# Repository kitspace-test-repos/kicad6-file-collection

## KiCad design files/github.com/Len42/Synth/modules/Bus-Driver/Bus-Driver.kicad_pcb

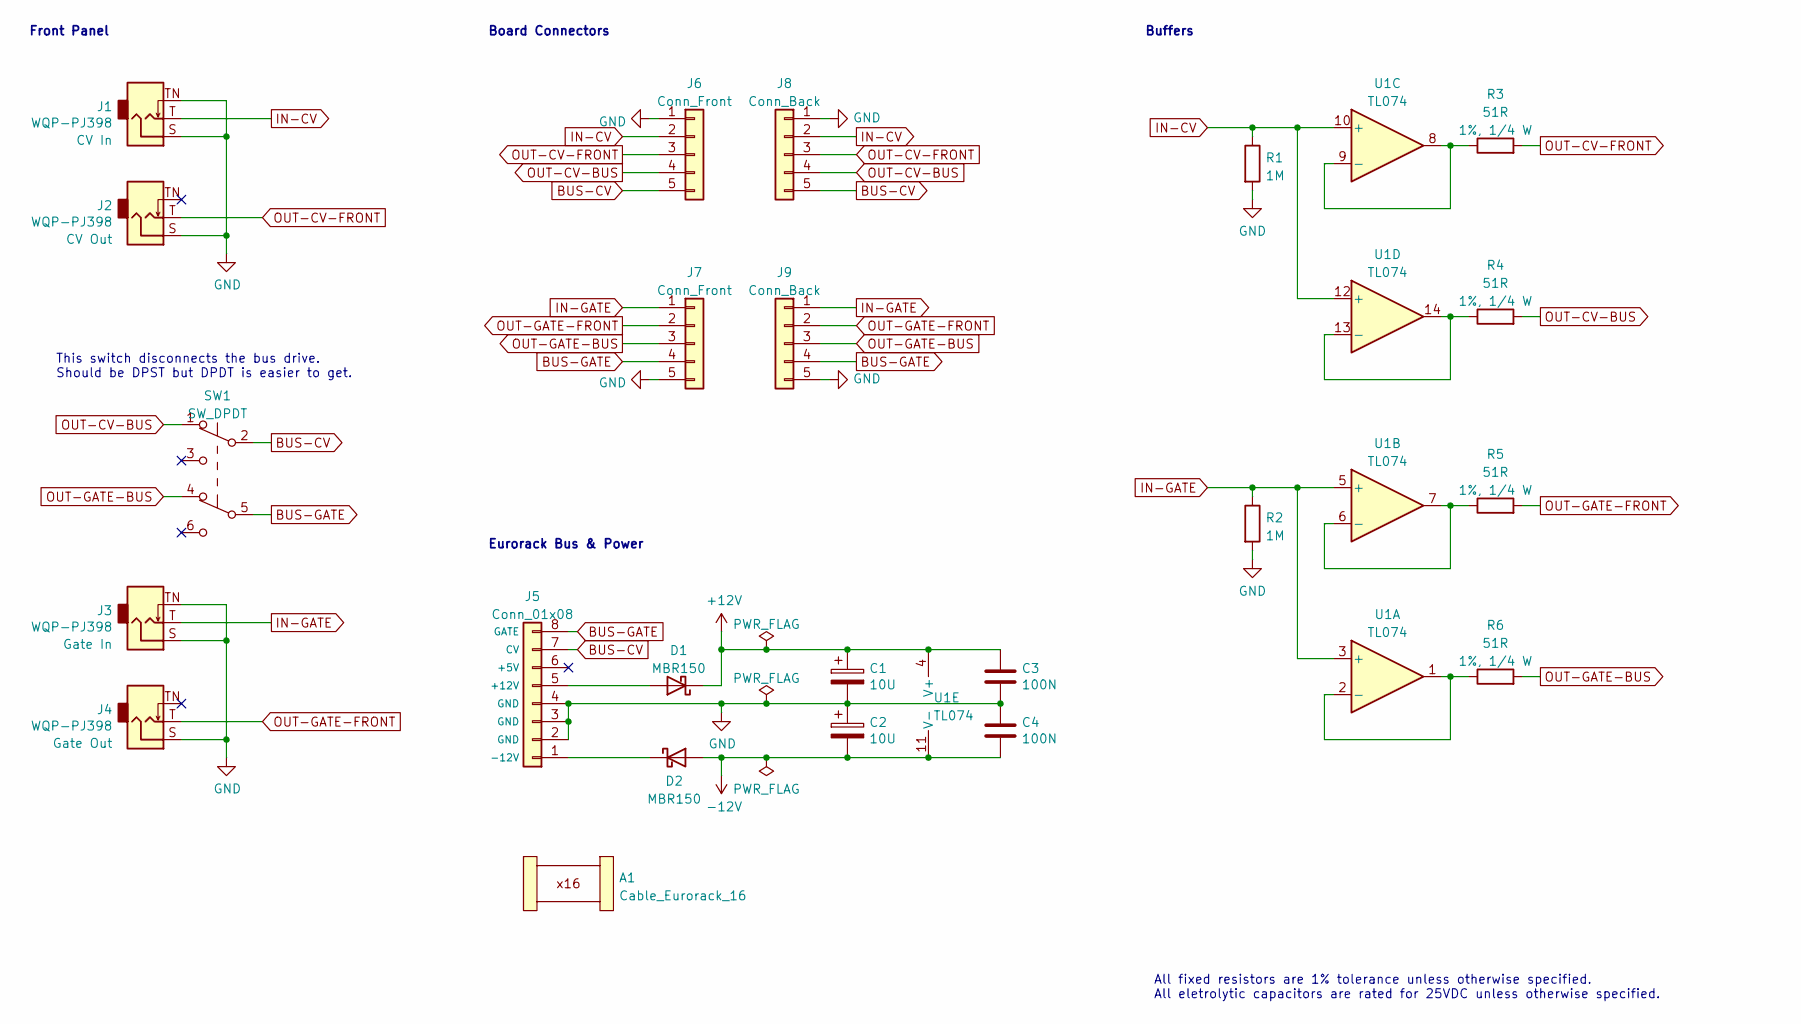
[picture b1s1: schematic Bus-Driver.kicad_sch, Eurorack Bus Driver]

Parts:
A1: Cable_Eurorack_16; NoFootprint
C1, C2: 10U; CP_Radial_D5.0mm_P2.50mm; ManufacturerPartNum ECE-A1VKS100I
C3, C4: 100N; C_Disc_D5.0mm_W2.5mm_P2.50mm; ManufacturerPartNum FG18X7R1H104KNT06
D1, D2: MBR150; D_DO-41_SOD81_P7.62mm_Horizontal; ManufacturerPartNum MBR150RLG
J1, J2, J3, J4: WQP-PJ398; Jack_3.5mm_QingPu_WQP-PJ398SM_Vertical; ManufacturerPartNum PJ398SM / WQP518MA
J5: Conn_01x08; PinHeader-Eurorack-8-TH-RA
J6, J7: Conn_Front; PinSocket_1x05_P2.54mm_Vertical
J8, J9: Conn_Back; PinHeader_1x05_P2.54mm_Horizontal
R1, R2: 1M; R_Axial_DIN0207_L6.3mm_D2.5mm_P7.62mm_Horizontal; ManufacturerPartNum MFR-12*
R3, R4, R5, R6: 51R; R_Axial_DIN0207_L6.3mm_D2.5mm_P10.16mm_Horizontal; ManufacturerPartNum MFR-25FBF52-51R
SW1: SW_DPDT; SW_DPDT_THT_2.54; ManufacturerPartNum 2S1-MDP1-T1-B1-M2QE
U1: TL074; DIP-14_W7.62mm; ManufacturerPartNum TL074BCN

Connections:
+12V: C1.1, C3.1, D1.1 (K), U1.4 (V+)
-12V: C2.2, C4.2, D2.2 (A), U1.11 (V-)
BUS-CV: J5.7 (CV), J6.5, J8.5, SW1.2 (B)
BUS-GATE: J5.8 (GATE), J7.4, J9.4, SW1.5 (B)
GND: C1.2, C2.1, C3.2, C4.1, J1.S, J1.TN, J2.S, J3.S, J3.TN, J4.S, J5.2 (GND), J5.3 (GND), J5.4 (GND), J6.1, J7.5, J8.1, J9.5, R1.2, R2.2
IN-CV: J1.T, J6.2, J8.2, R1.1, U1.10 (+), U1.12 (+)
IN-GATE: J3.T, J7.1, J9.1, R2.1, U1.3 (+), U1.5 (+)
unnamed: D1.2 (A), J5.5 (+12V)
unnamed: D2.1 (K), J5.1 (-12V)
unnamed: R3.1, U1.8, U1.9 (-)
unnamed: R4.1, U1.13 (-), U1.14
unnamed: R5.1, U1.6 (-), U1.7
unnamed: R6.1, U1.1, U1.2 (-)
OUT-CV-BUS: J6.4, J8.4, R4.2, SW1.1 (A)
OUT-CV-FRONT: J2.T, J6.3, J8.3, R3.2
OUT-GATE-BUS: J7.3, J9.3, R6.2, SW1.4 (A)
OUT-GATE-FRONT: J4.T, J7.2, J9.2, R5.2

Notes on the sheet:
All fixed resistors are 1% tolerance unless otherwise specified. All eletrolytic capacitors are rated for 25VDC unless otherwise specified.
Board Connectors
Front Panel
This switch disconnects the bus drive. Should be DPST but DPDT is easier to get.
Eurorack Bus & Power
Buffers

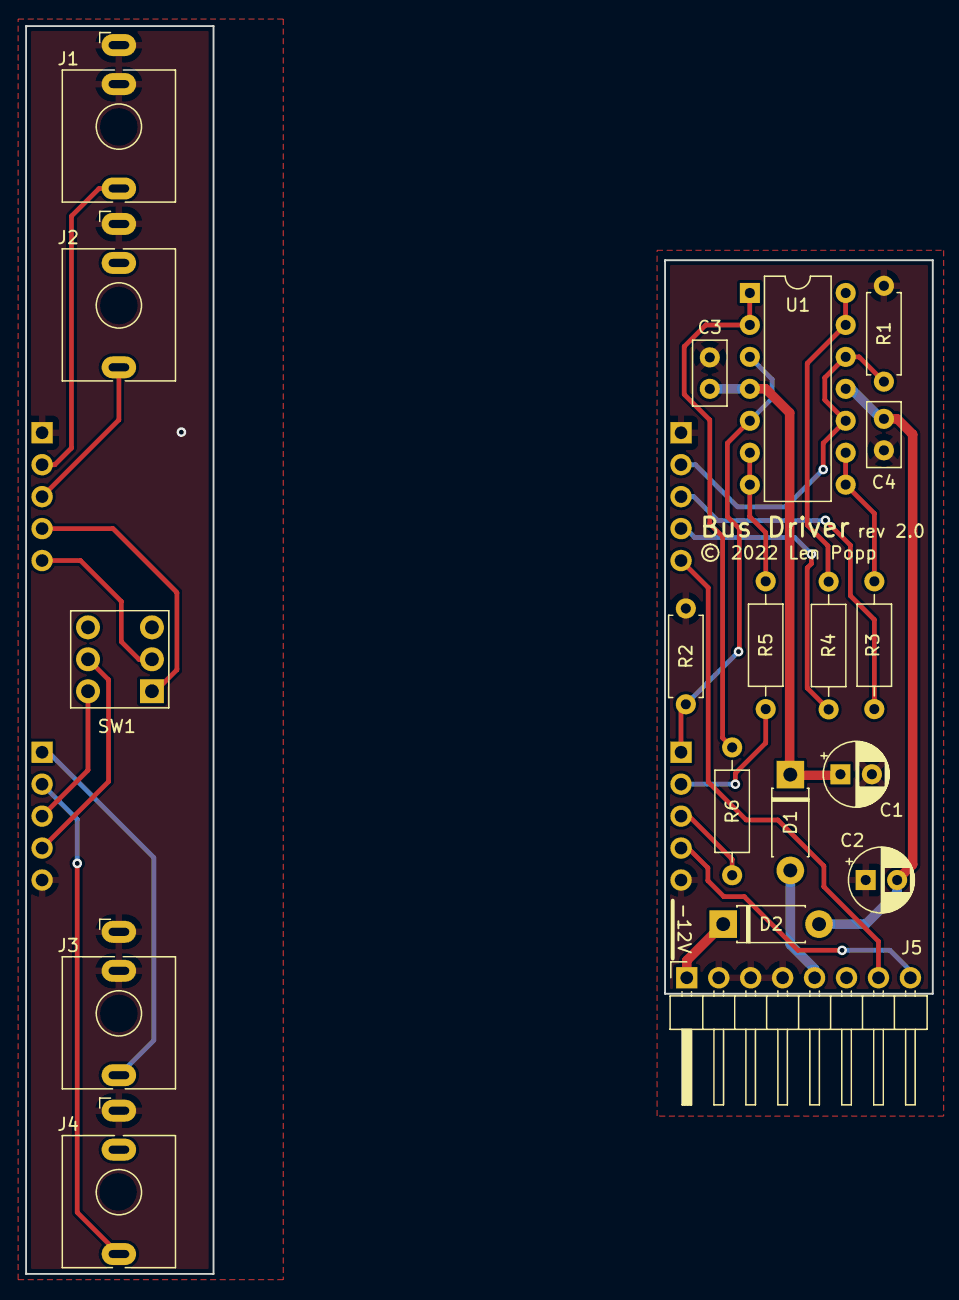
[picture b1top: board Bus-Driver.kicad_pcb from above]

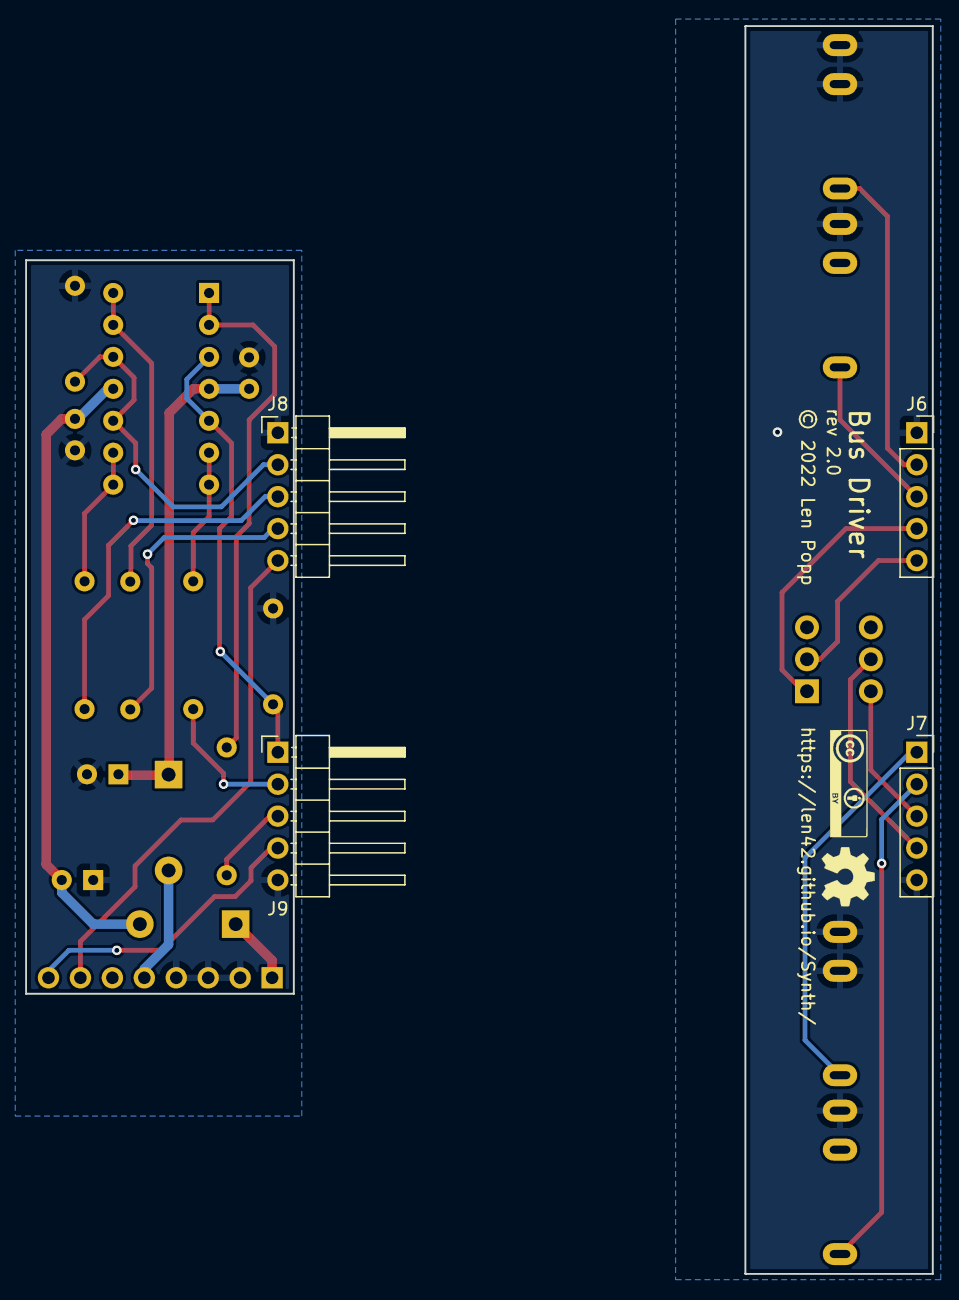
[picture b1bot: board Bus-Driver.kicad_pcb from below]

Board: 2 copper layers, 72.1 x 99.2 mm, 25 parts (6 on the bottom side), 17 nets.

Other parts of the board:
G2: Logo_CC_BY
G4: Logo_OSHW

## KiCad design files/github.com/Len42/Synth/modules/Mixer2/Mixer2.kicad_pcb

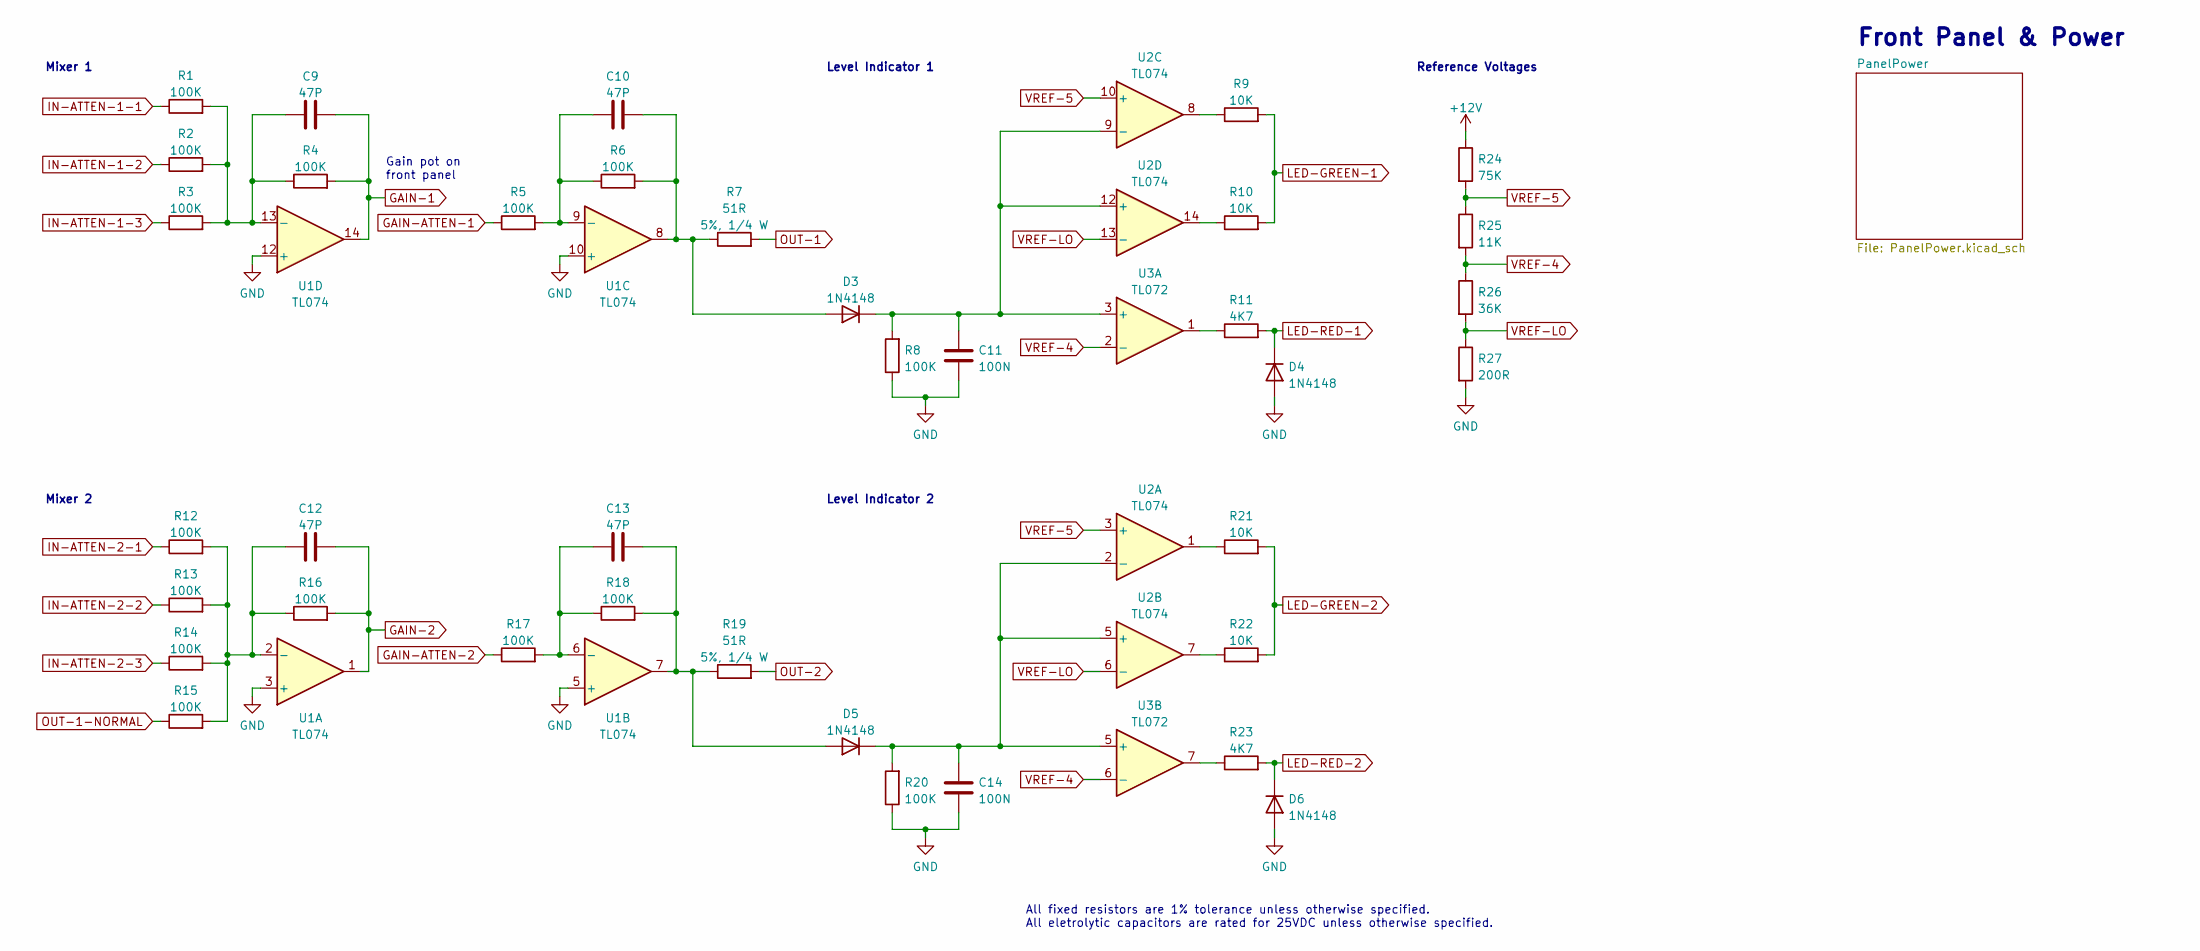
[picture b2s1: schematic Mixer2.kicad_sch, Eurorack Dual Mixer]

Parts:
C9, C10, C12, C13: 47P; C_Disc_D5.0mm_W2.5mm_P2.50mm; ManufacturerPartNum K470K15C0GH53L2
C11, C14: 100N; C_Disc_D5.0mm_W2.5mm_P2.50mm; ManufacturerPartNum FG18X7R1H104KNT06
D3, D4, D5, D6: 1N4148; D_DO-35_SOD27_P7.62mm_Horizontal; ManufacturerPartNum 1N4148-T50R
R1, R2, R3, R4, R5, R6, R8, R12, R13, R14, R15, R16, R17, R18, R20: 100K; R_Axial_DIN0207_L6.3mm_D2.5mm_P7.62mm_Horizontal; ManufacturerPartNum MFR-12FTF52-100K
R7, R19: 51R; R_Axial_DIN0207_L6.3mm_D2.5mm_P10.16mm_Horizontal; ManufacturerPartNum MFR-25FBF52-51R
R9, R10, R21, R22: 10K; R_Axial_DIN0207_L6.3mm_D2.5mm_P7.62mm_Horizontal; ManufacturerPartNum MFR-12FTF52-10K
R11, R23: 4K7; R_Axial_DIN0207_L6.3mm_D2.5mm_P7.62mm_Horizontal; ManufacturerPartNum MFR-12FTF52-4K7
R24: 75K; R_Axial_DIN0207_L6.3mm_D2.5mm_P7.62mm_Horizontal; ManufacturerPartNum MFR-12FTF52-75K
R25: 11K; R_Axial_DIN0207_L6.3mm_D2.5mm_P7.62mm_Horizontal; ManufacturerPartNum MFR-12FTF52-11K
R26: 36K; R_Axial_DIN0207_L6.3mm_D2.5mm_P7.62mm_Horizontal; ManufacturerPartNum MFR-12FTF52-36K
R27: 200R; R_Axial_DIN0207_L6.3mm_D2.5mm_P7.62mm_Horizontal; ManufacturerPartNum MFR-12FTF52-200R
U1, U2: TL074; DIP-14_W7.62mm; ManufacturerPartNum TL074BCN
U3: TL072; DIP-8_W7.62mm; ManufacturerPartNum TL072BCP

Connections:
+12V: R24.1; also elsewhere on the board
GAIN-1: C9.2, R4.2, U1.14; also elsewhere on the board
GAIN-2: C12.2, R16.2, U1.1; also elsewhere on the board
GAIN-ATTEN-1: R5.1; also elsewhere on the board
GAIN-ATTEN-2: R17.1; also elsewhere on the board
GND: C11.2, C14.2, D4.2 (A), D6.2 (A), R8.1, R20.1, R27.2, U1.3 (+), U1.5 (+), U1.10 (+), U1.12 (+); also elsewhere on the board
IN-ATTEN-1-1: R1.1; also elsewhere on the board
IN-ATTEN-1-2: R2.1; also elsewhere on the board
IN-ATTEN-1-3: R3.1; also elsewhere on the board
IN-ATTEN-2-1: R12.1; also elsewhere on the board
IN-ATTEN-2-2: R13.1; also elsewhere on the board
IN-ATTEN-2-3: R14.1; also elsewhere on the board
LED-GREEN-1: R9.2, R10.2; also elsewhere on the board
LED-GREEN-2: R21.2, R22.2; also elsewhere on the board
LED-RED-1: D4.1 (K), R11.2; also elsewhere on the board
LED-RED-2: D6.1 (K), R23.2; also elsewhere on the board
unnamed: C9.1, R1.2, R2.2, R3.2, R4.1, U1.13 (-)
unnamed: C10.1, R5.2, R6.1, U1.9 (-)
unnamed: C10.2, D3.2 (A), R6.2, R7.1, U1.8
unnamed: C11.1, D3.1 (K), R8.2, U2.9 (-), U2.12 (+), U3.3 (+)
unnamed: C12.1, R12.2, R13.2, R14.2, R15.2, R16.1, U1.2 (-)
unnamed: C13.1, R17.2, R18.1, U1.6 (-)
unnamed: C13.2, D5.2 (A), R18.2, R19.1, U1.7
unnamed: C14.1, D5.1 (K), R20.2, U2.2 (-), U2.5 (+), U3.5 (+)
unnamed: R9.1, U2.8
unnamed: R10.1, U2.14
unnamed: R11.1, U3.1
unnamed: R21.1, U2.1
unnamed: R22.1, U2.7
unnamed: R23.1, U3.7
OUT-1: R7.2; also elsewhere on the board
OUT-1-NORMAL: R15.1; also elsewhere on the board
OUT-2: R19.2; also elsewhere on the board
VREF-4: R25.2, R26.1, U3.2 (-), U3.6 (-)
VREF-5: R24.2, R25.1, U2.3 (+), U2.10 (+)
VREF-LO: R26.2, R27.1, U2.6 (-), U2.13 (-)

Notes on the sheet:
Reference Voltages
All fixed resistors are 1% tolerance unless otherwise specified. All eletrolytic capacitors are rated for 25VDC unless otherwise specified.
Gain pot on front panel
Level Indicator 1
Level Indicator 2
Mixer 1
Mixer 2
Front Panel & Power

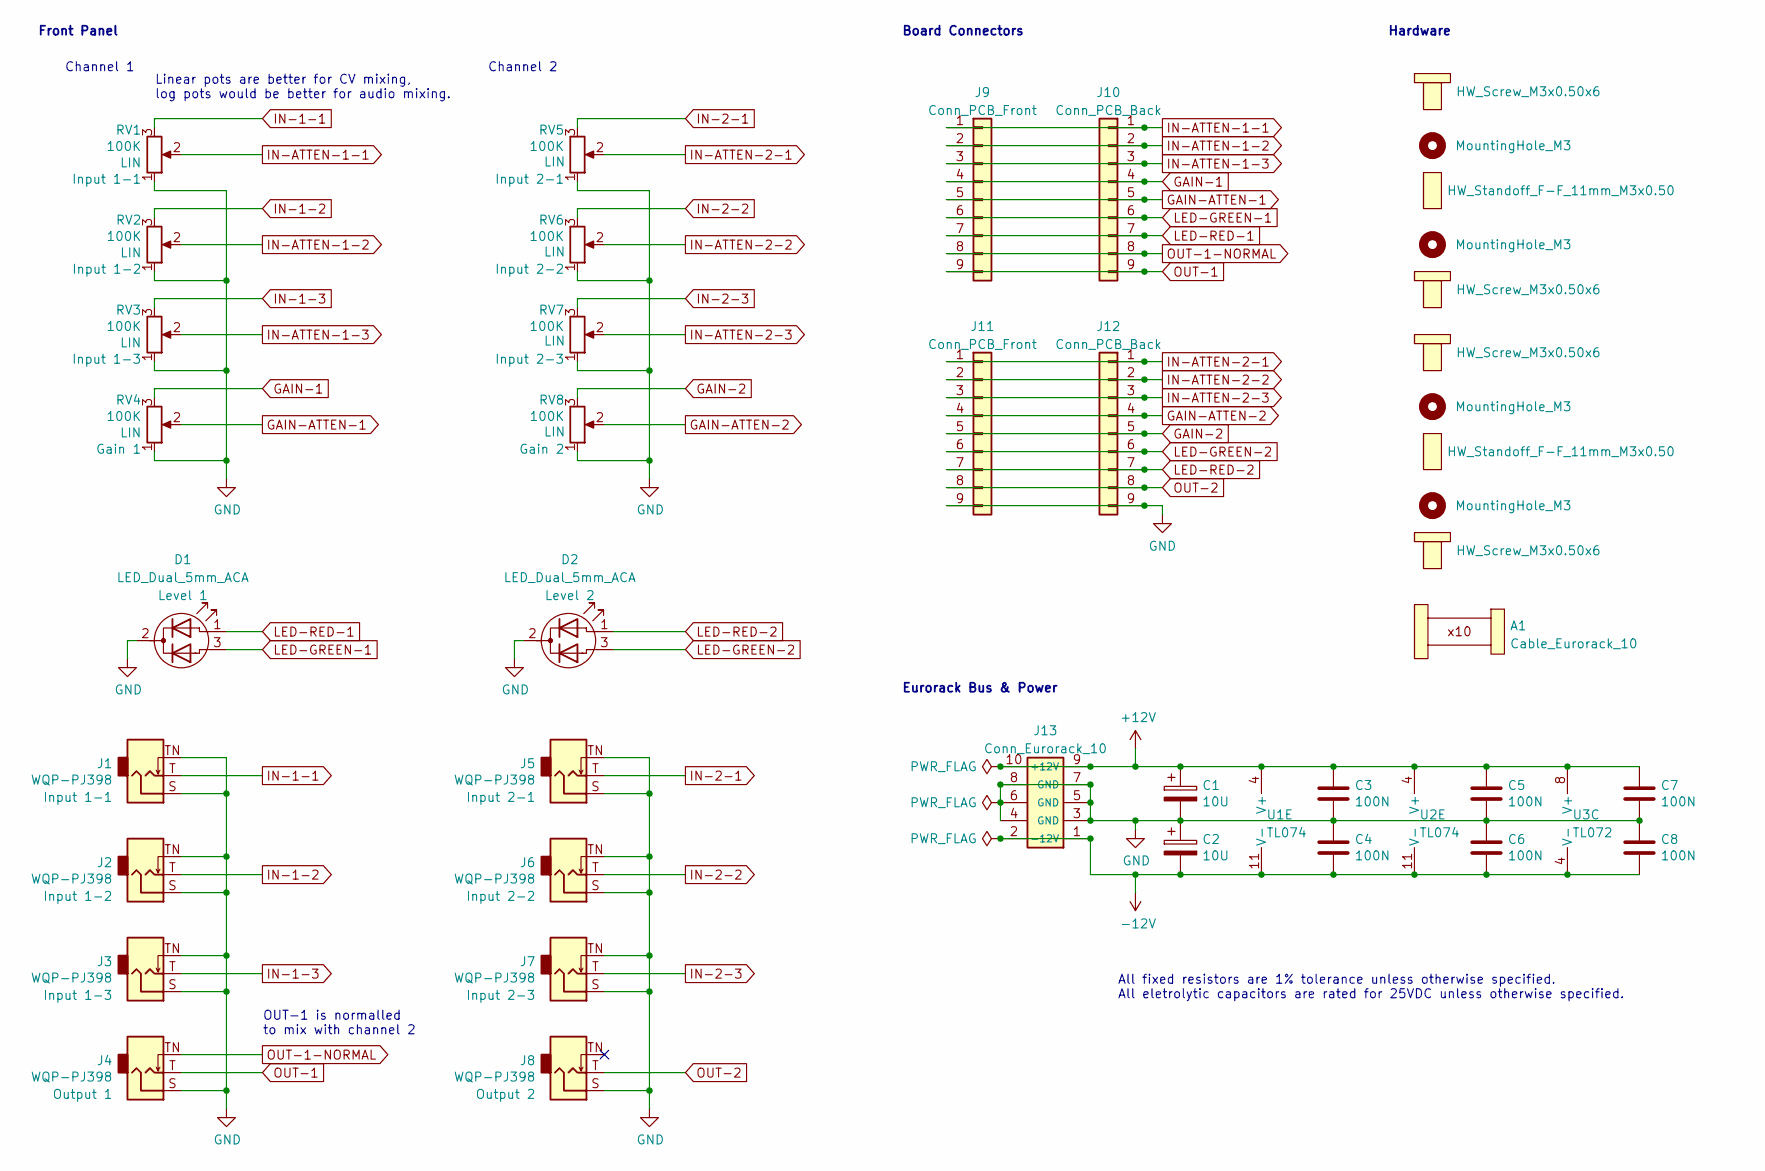
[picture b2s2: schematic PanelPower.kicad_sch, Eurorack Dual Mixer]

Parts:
A1: Cable_Eurorack_10; NoFootprint
C1, C2: 10U; CP_Radial_D5.0mm_P2.50mm; ManufacturerPartNum ECE-A1VKS100I
C3, C4, C5, C6, C7, C8: 100N; C_Disc_D5.0mm_W2.5mm_P2.50mm; ManufacturerPartNum FG18X7R1H104KNT06
D1, D2: LED_Dual_5mm_ACA; LED_D5.0mm-3; ManufacturerPartNum WP59SURKCGKW
H1, H5, H6, H10: HW_Screw_M3x0.50x6
H2, H4, H7, H9: MountingHole_M3; MountingHole_PCB_3.2mm_M3
H3, H8: HW_Standoff_F-F_11mm_M3x0.50; ManufacturerPartNum 05.03.111
J1, J2, J3, J4, J5, J6, J7, J8: WQP-PJ398; Jack_3.5mm_QingPu_WQP-PJ398SM_Vertical; ManufacturerPartNum PJ398SM / WQP518MA
J9, J11: Conn_PCB_Front; PinSocket_1x09_P2.54mm_Vertical
J10, J12: Conn_PCB_Back; PinHeader_1x09_P2.54mm_Vertical
J13: Conn_Eurorack_10; IDC-Header-Eurorack-10-TH; ManufacturerPartNum 61201021621
RV1, RV2, RV3, RV4, RV5, RV6, RV7, RV8: 100K; Potentiometer_Alpha_RD901F-40-00D_Single_Vertical; ManufacturerPartNum RD901F-*
U1, U2: TL074; DIP-14_W7.62mm; ManufacturerPartNum TL074BCN
U3: TL072; DIP-8_W7.62mm; ManufacturerPartNum TL072BCP

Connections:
+12V: C1.1, C3.1, C5.1, C7.1, J13.9 (+12V), J13.10, U1.4 (V+), U2.4 (V+), U3.8 (V+); also elsewhere on the board
-12V: C2.2, C4.2, C6.2, C8.2, J13.1 (-12V), J13.2, U1.11 (V-), U2.11 (V-), U3.4 (V-)
GAIN-1: J9.4, J10.4, RV4.3; also elsewhere on the board
GAIN-2: J11.5, J12.5, RV8.3; also elsewhere on the board
GAIN-ATTEN-1: J9.5, J10.5, RV4.2; also elsewhere on the board
GAIN-ATTEN-2: J11.4, J12.4, RV8.2; also elsewhere on the board
GND: C1.2, C2.1, C3.2, C4.1, C5.2, C6.1, C7.2, C8.1, D1.2 (K), D2.2 (K), J1.S, J1.TN, J2.S, J2.TN, J3.S, J3.TN, J4.S, J5.S, J5.TN, J6.S, J6.TN, J7.S, J7.TN, J8.S, J11.9, J12.9, J13.3 (GND), J13.4, J13.5 (GND), J13.6, J13.7 (GND), J13.8, RV1.1, RV2.1, RV3.1, RV4.1, RV5.1, RV6.1, RV7.1, RV8.1; also elsewhere on the board
IN-1-1: J1.T, RV1.3
IN-1-2: J2.T, RV2.3
IN-1-3: J3.T, RV3.3
IN-2-1: J5.T, RV5.3
IN-2-2: J6.T, RV6.3
IN-2-3: J7.T, RV7.3
IN-ATTEN-1-1: J9.1, J10.1, RV1.2; also elsewhere on the board
IN-ATTEN-1-2: J9.2, J10.2, RV2.2; also elsewhere on the board
IN-ATTEN-1-3: J9.3, J10.3, RV3.2; also elsewhere on the board
IN-ATTEN-2-1: J11.1, J12.1, RV5.2; also elsewhere on the board
IN-ATTEN-2-2: J11.2, J12.2, RV6.2; also elsewhere on the board
IN-ATTEN-2-3: J11.3, J12.3, RV7.2; also elsewhere on the board
LED-GREEN-1: D1.3 (A2), J9.6, J10.6; also elsewhere on the board
LED-GREEN-2: D2.3 (A2), J11.6, J12.6; also elsewhere on the board
LED-RED-1: D1.1 (A1), J9.7, J10.7; also elsewhere on the board
LED-RED-2: D2.1 (A1), J11.7, J12.7; also elsewhere on the board
OUT-1: J4.T, J9.9, J10.9; also elsewhere on the board
OUT-1-NORMAL: J4.TN, J9.8, J10.8; also elsewhere on the board
OUT-2: J8.T, J11.8, J12.8; also elsewhere on the board

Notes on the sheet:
Hardware
All fixed resistors are 1% tolerance unless otherwise specified. All eletrolytic capacitors are rated for 25VDC unless otherwise specified.
Front Panel
Board Connectors
Linear pots are better for CV mixing, log pots would be better for audio mixing.
OUT-1 is normalled to mix with channel 2
Eurorack Bus & Power
Channel 1
Channel 2

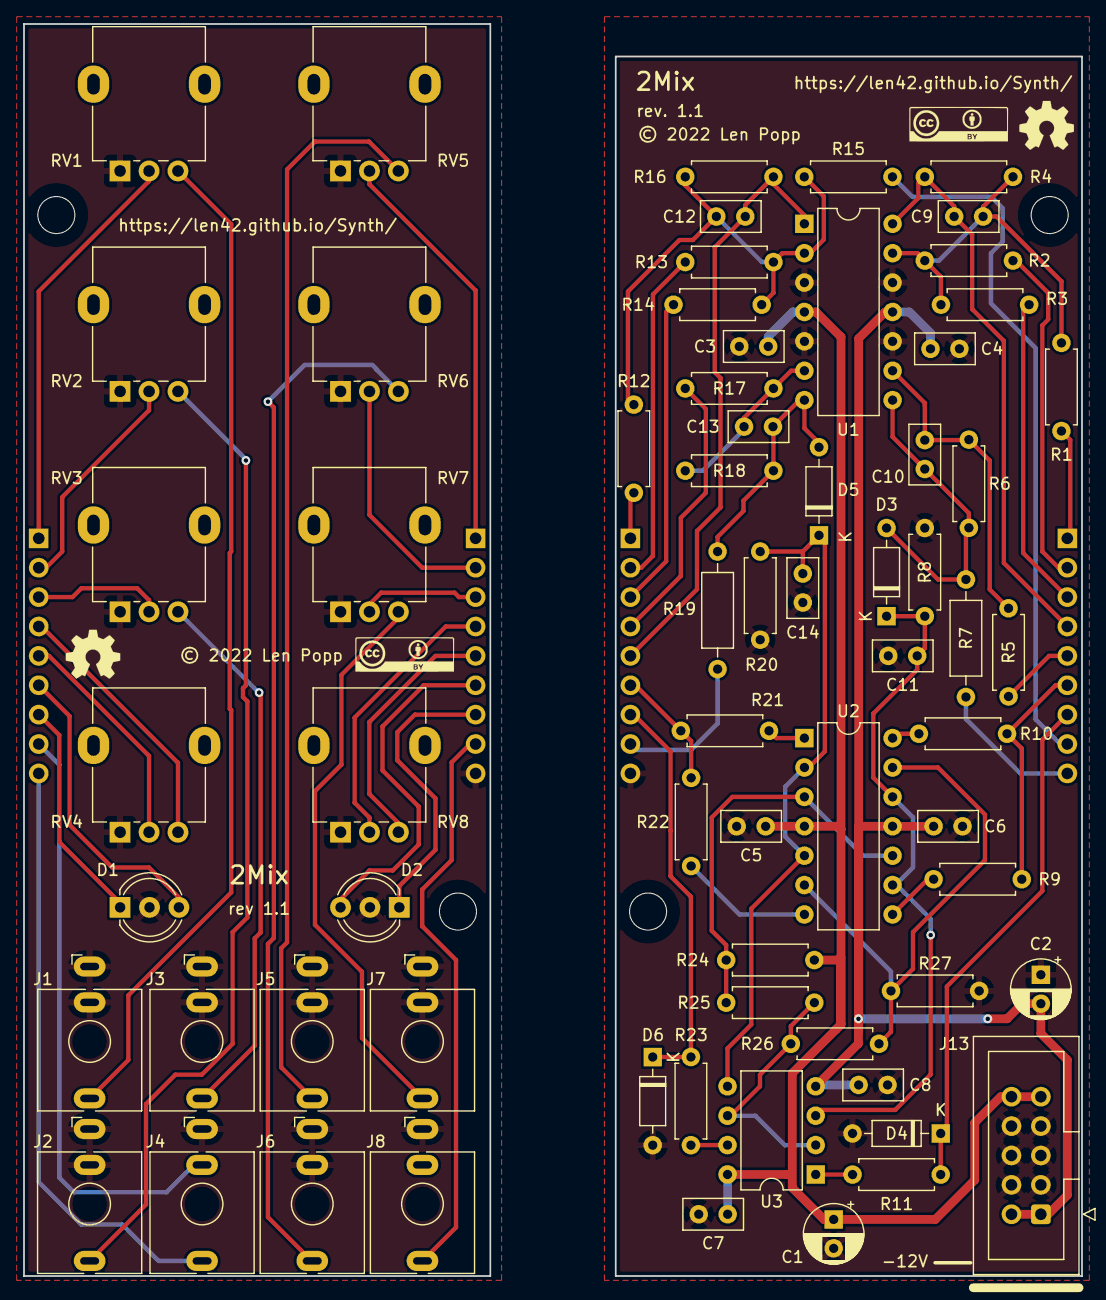
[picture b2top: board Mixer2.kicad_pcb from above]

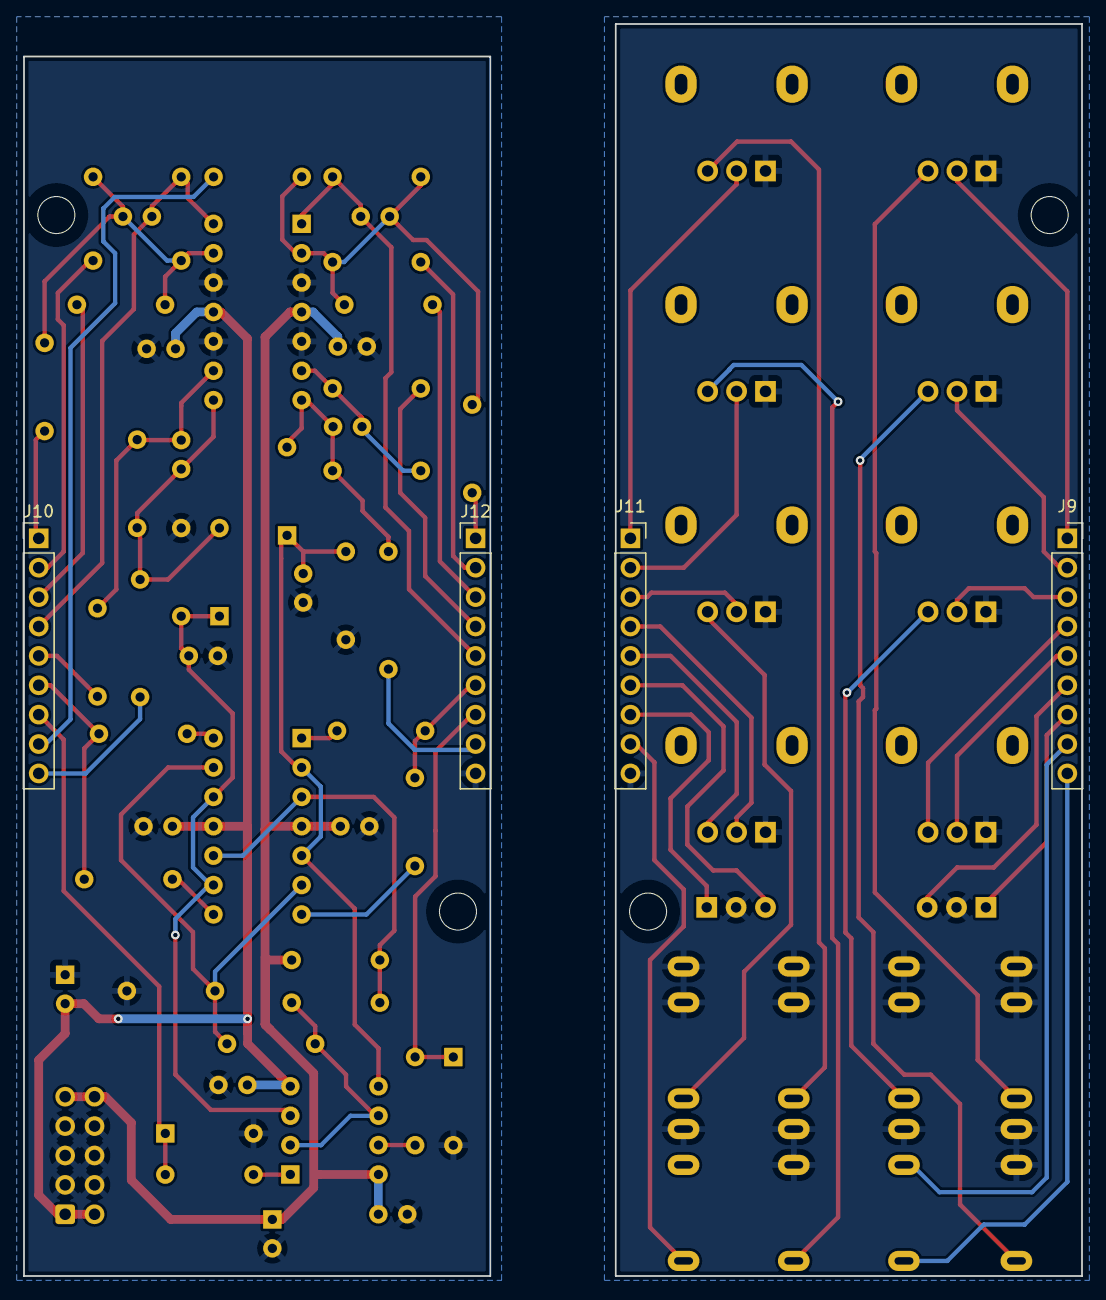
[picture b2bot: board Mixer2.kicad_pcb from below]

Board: 2 copper layers, 91.4 x 108.2 mm, 79 parts (4 on the bottom side), 43 nets.

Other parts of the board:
G1, G2: Logo_CC_BY
G3, G4: Logo_OSHW

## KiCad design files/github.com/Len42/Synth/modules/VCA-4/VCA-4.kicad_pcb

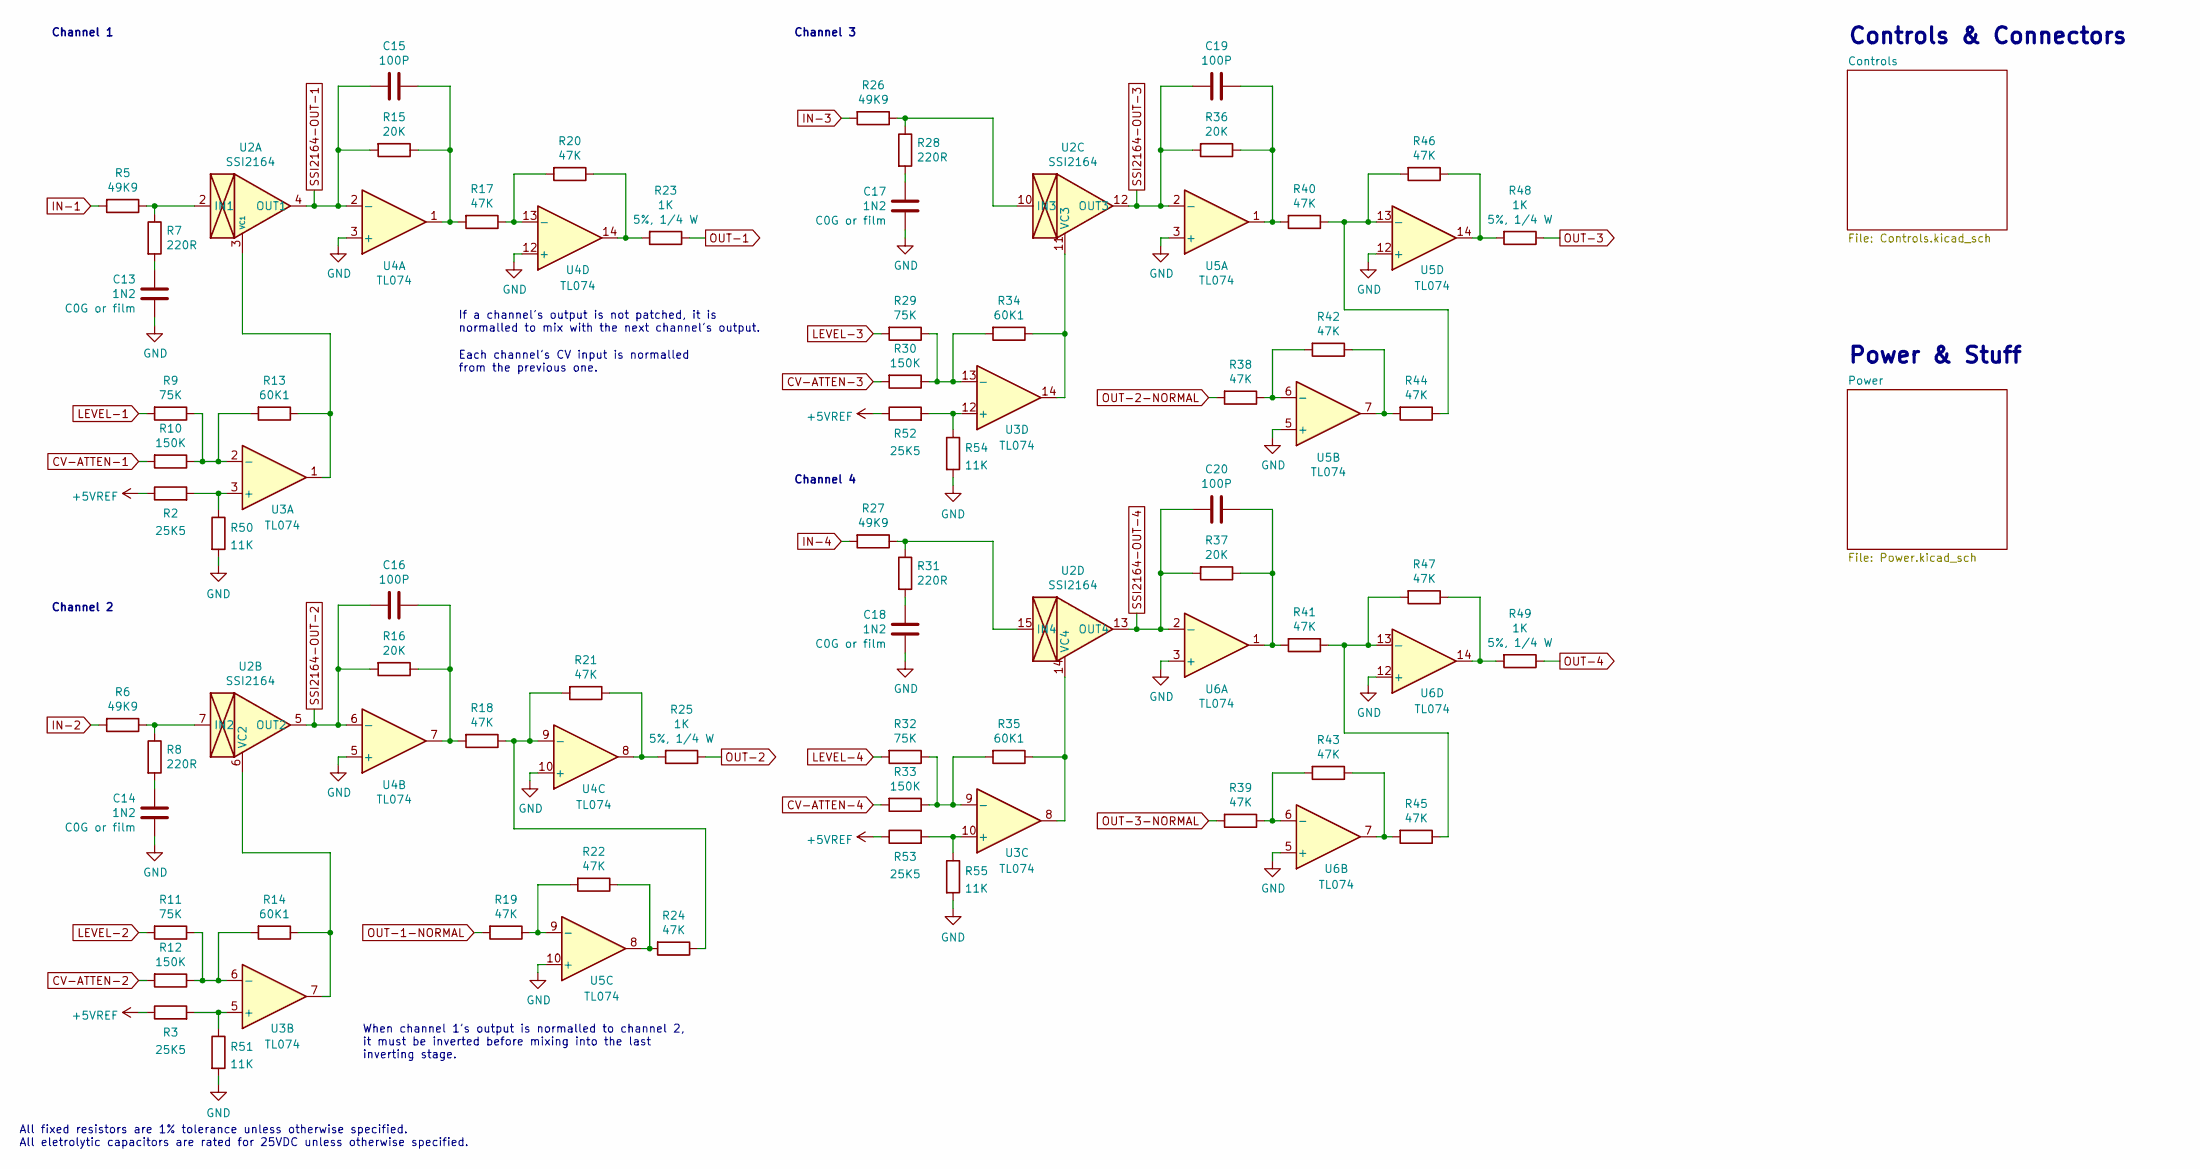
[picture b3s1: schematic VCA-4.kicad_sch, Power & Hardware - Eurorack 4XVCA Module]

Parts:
C13, C14, C17, C18: 1N2; C_Rect_Kemet_L7.2mm_W2.5mm_P5mm; ManufacturerPartNum R82EC1120DQ50J
C15, C16, C19, C20: 100P; C_Disc_D5.0mm_W2.5mm_P2.50mm; ManufacturerPartNum K101J15C0GF53L2
R2, R3, R52, R53: 25K5; R_Axial_DIN0207_L6.3mm_D2.5mm_P7.62mm_Horizontal; ManufacturerPartNum MFR-25FRF52-25K5
R5, R6, R26, R27: 49K9; R_Axial_DIN0207_L6.3mm_D2.5mm_P10.16mm_Horizontal; ManufacturerPartNum RN55D4992FB14
R7, R8, R28, R31: 220R; R_Axial_DIN0207_L6.3mm_D2.5mm_P7.62mm_Horizontal; ManufacturerPartNum MFR-12FTF52-220R
R9, R11, R29, R32: 75K; R_Axial_DIN0207_L6.3mm_D2.5mm_P7.62mm_Horizontal; ManufacturerPartNum MFR-12FTF52-75K
R10, R12, R30, R33: 150K; R_Axial_DIN0207_L6.3mm_D2.5mm_P7.62mm_Horizontal; ManufacturerPartNum MFR-12FTF52-150K
R13, R14, R34, R35: 60K1; R_Axial_DIN0207_L6.3mm_D2.5mm_P10.16mm_Horizontal; ManufacturerPartNum RN55D6012FB14
R15, R16, R36, R37: 20K; R_Axial_DIN0207_L6.3mm_D2.5mm_P7.62mm_Horizontal; ManufacturerPartNum MFR-12FTF52-20K
R17, R18, R19, R20, R21, R22, R24, R38, R39, R40, R41, R42, R43, R44, R45, R46, R47: 47K; R_Axial_DIN0207_L6.3mm_D2.5mm_P7.62mm_Horizontal; ManufacturerPartNum MFR-12FTF52-47K
R23, R25, R48, R49: 1K; R_Axial_DIN0207_L6.3mm_D2.5mm_P10.16mm_Horizontal; ManufacturerPartNum CCF071K00JKE36
R50, R51, R54, R55: 11K; R_Axial_DIN0207_L6.3mm_D2.5mm_P7.62mm_Horizontal; ManufacturerPartNum MFR-12FTF52-11K
U2: SSI2164; Breakout_DIP-SOIC-16_W15.24mm; ManufacturerPartNum SSI2164
U3, U4, U5, U6: TL074; DIP-14_W7.62mm; ManufacturerPartNum TL074BCN

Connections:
+5VREF: R2.1, R3.1, R52.1, R53.1; also elsewhere on the board
CV-ATTEN-1: R10.2; also elsewhere on the board
CV-ATTEN-2: R12.2; also elsewhere on the board
CV-ATTEN-3: R30.2; also elsewhere on the board
CV-ATTEN-4: R33.2; also elsewhere on the board
GND: C13.2, C14.2, C17.2, C18.2, R50.2, R51.2, R54.2, R55.2, U4.3 (+), U4.5 (+), U4.10 (+), U4.12 (+), U5.3 (+), U5.5 (+), U5.10 (+), U5.12 (+), U6.3 (+), U6.5 (+), U6.12 (+); also elsewhere on the board
IN-1: R5.2; also elsewhere on the board
IN-2: R6.2; also elsewhere on the board
IN-3: R26.2; also elsewhere on the board
IN-4: R27.2; also elsewhere on the board
LEVEL-1: R9.2; also elsewhere on the board
LEVEL-2: R11.2; also elsewhere on the board
LEVEL-3: R29.2; also elsewhere on the board
LEVEL-4: R32.2; also elsewhere on the board
unnamed: C13.1, R7.2
unnamed: C14.1, R8.2
unnamed: C15.1, R15.1, R17.2, U4.1
unnamed: C16.1, R16.1, R18.2, U4.7
unnamed: C17.1, R28.2
unnamed: C18.1, R31.2
unnamed: C19.1, R36.1, R40.2, U5.1
unnamed: C20.1, R37.1, R41.2, U6.1
unnamed: R2.2, R50.1, U3.3 (+)
unnamed: R3.2, R51.1, U3.5 (+)
unnamed: R5.1, R7.1, U2.2 (IN1)
unnamed: R6.1, R8.1, U2.7 (IN2)
unnamed: R9.1, R10.1, R13.2, U3.2 (-)
unnamed: R11.1, R12.1, R14.2, U3.6 (-)
unnamed: R13.1, U2.3 (VC1), U3.1
unnamed: R14.1, U2.6 (VC2), U3.7
unnamed: R17.1, R20.2, U4.13 (-)
unnamed: R18.1, R21.2, R24.1, U4.9 (-)
unnamed: R19.1, R22.2, U5.9 (-)
unnamed: R20.1, R23.2, U4.14
unnamed: R21.1, R25.2, U4.8
unnamed: R22.1, R24.2, U5.8
unnamed: R26.1, R28.1, U2.10 (IN3)
unnamed: R27.1, R31.1, U2.15 (IN4)
unnamed: R29.1, R30.1, R34.2, U3.13 (-)
unnamed: R32.1, R33.1, R35.2, U3.9 (-)
unnamed: R34.1, U2.11 (VC3), U3.14
unnamed: R35.1, U2.14 (VC4), U3.8
unnamed: R38.1, R42.2, U5.6 (-)
unnamed: R39.1, R43.2, U6.6 (-)
unnamed: R40.1, R44.1, R46.2, U5.13 (-)
unnamed: R41.1, R45.1, R47.2, U6.13 (-)
unnamed: R42.1, R44.2, U5.7
unnamed: R43.1, R45.2, U6.7
unnamed: R46.1, R48.2, U5.14
unnamed: R47.1, R49.2, U6.14
unnamed: R52.2, R54.1, U3.12 (+)
unnamed: R53.2, R55.1, U3.10 (+)
OUT-1: R23.1; also elsewhere on the board
OUT-1-NORMAL: R19.2; also elsewhere on the board
OUT-2: R25.1; also elsewhere on the board
OUT-2-NORMAL: R38.2; also elsewhere on the board
OUT-3: R48.1; also elsewhere on the board
OUT-3-NORMAL: R39.2; also elsewhere on the board
OUT-4: R49.1; also elsewhere on the board
SSI2164-OUT-1: C15.2, R15.2, U2.4 (OUT1), U4.2 (-); also elsewhere on the board
SSI2164-OUT-2: C16.2, R16.2, U2.5 (OUT2), U4.6 (-); also elsewhere on the board
SSI2164-OUT-3: C19.2, R36.2, U2.12 (OUT3), U5.2 (-); also elsewhere on the board
SSI2164-OUT-4: C20.2, R37.2, U2.13 (OUT4), U6.2 (-); also elsewhere on the board

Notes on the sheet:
When channel 1's output is normalled to channel 2, it must be inverted before mixing into the last inverting stage.
Power & Stuff
All fixed resistors are 1% tolerance unless otherwise specified. All eletrolytic capacitors are rated for 25VDC unless otherwise specified.
Channel 2
Channel 3
Channel 4
Controls & Connectors
Each channel's CV input is normalled from the previous one.
Channel 1
If a channel's output is not patched, it is normalled to mix with the next channel's output.

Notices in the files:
files/github.com/Len42/Synth/modules/Audiout/PanelPower.kicad_sch:
Copyright © 2022 Len Popp CC BY
files/github.com/Len42/Synth/modules/VCA-4/Controls.kicad_sch:
Copyright © 2021 Len Popp CC BY
